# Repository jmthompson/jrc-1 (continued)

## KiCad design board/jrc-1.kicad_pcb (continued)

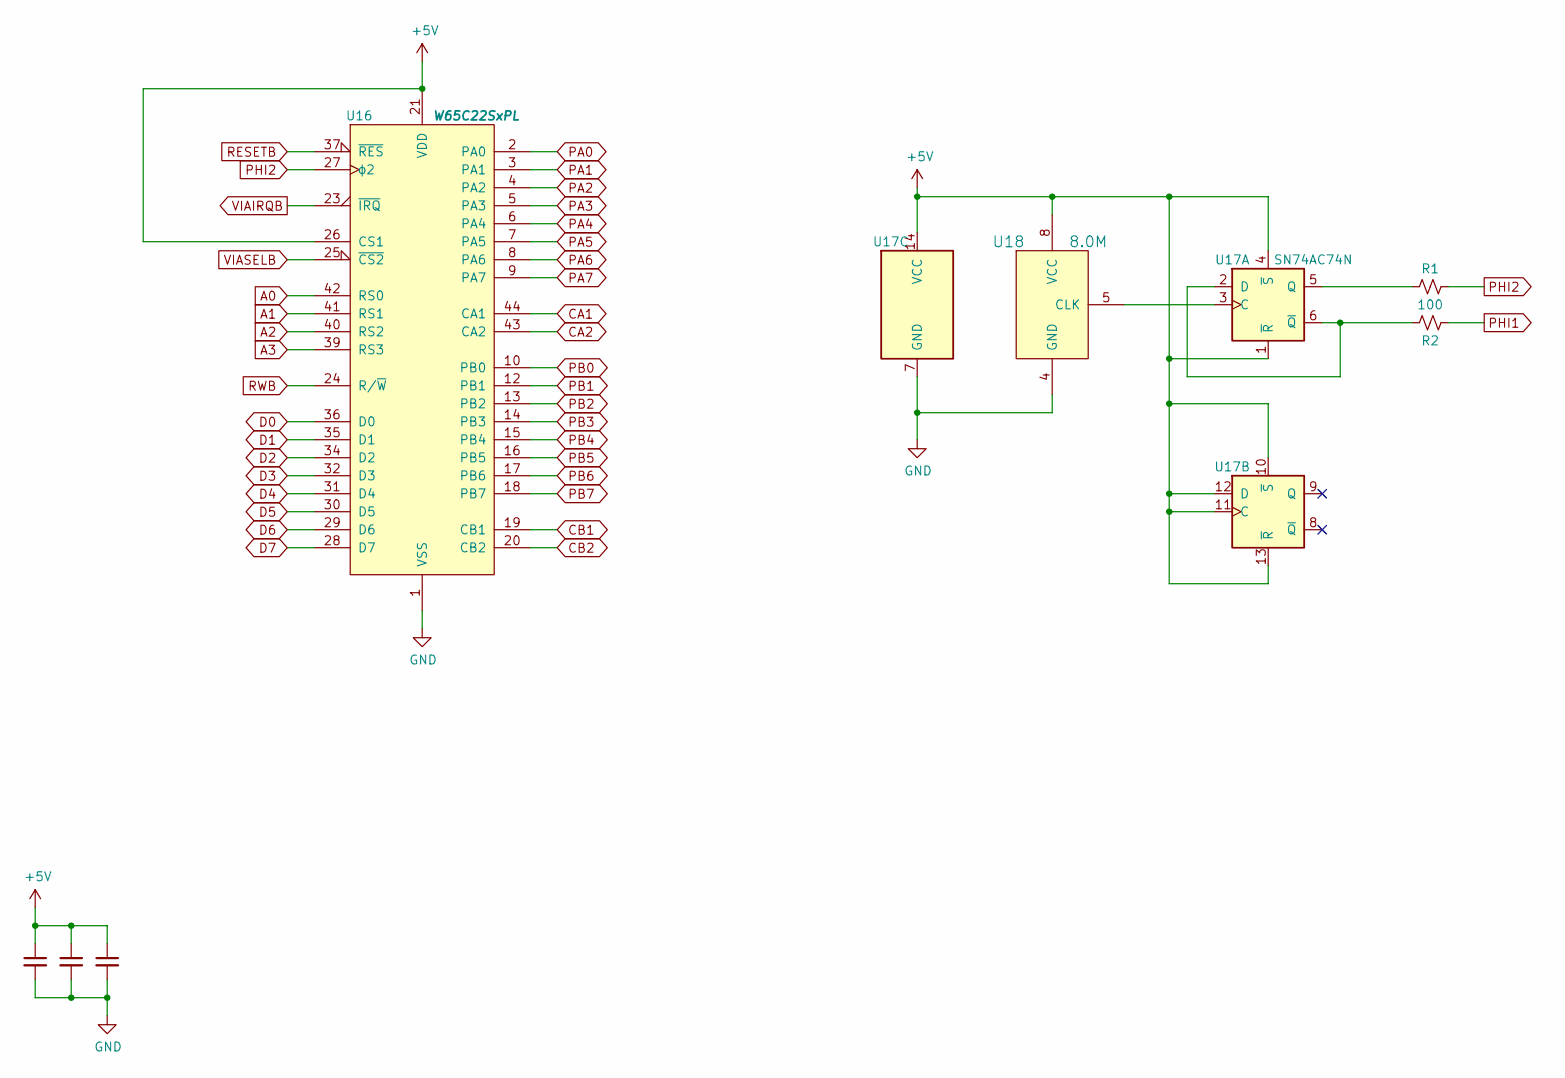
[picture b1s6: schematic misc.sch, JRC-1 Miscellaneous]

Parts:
C35, C36, C37: 0.1u; C_Rect_L4.6mm_W2.0mm_P2.50mm_MKS02_FKP02
R1, R2: 100; R_Axial_DIN0207_L6.3mm_D2.5mm_P10.16mm_Horizontal
U16: W65C22SxPL; PLCC-44_THT-Socket
U17: SN74AC74N; DIP-14_W7.62mm_Socket
U18: 8.0M; DIP-8_W7.62mm_Socket

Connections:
+5V: C35.1, C36.1, C37.1, U16.21 (VDD), U16.26 (CS1), U17.1 (~R), U17.4 (~S), U17.10 (~S), U17.11 (C), U17.12 (D), U17.13 (~R), U17.14 (VCC), U18.8 (VCC); also elsewhere on the board
A0: U16.42 (RS0); also elsewhere on the board
A1: U16.41 (RS1); also elsewhere on the board
A2: U16.40 (RS2); also elsewhere on the board
A3: U16.39 (RS3); also elsewhere on the board
CA1: U16.44 (CA1); also elsewhere on the board
CA2: U16.43 (CA2); also elsewhere on the board
CB1: U16.19 (CB1); also elsewhere on the board
CB2: U16.20 (CB2); also elsewhere on the board
D0: U16.36 (D0); also elsewhere on the board
D1: U16.35 (D1); also elsewhere on the board
D2: U16.34 (D2); also elsewhere on the board
D3: U16.32 (D3); also elsewhere on the board
D4: U16.31 (D4); also elsewhere on the board
D5: U16.30 (D5); also elsewhere on the board
D6: U16.29 (D6); also elsewhere on the board
D7: U16.28 (D7); also elsewhere on the board
GND: C35.2, C36.2, C37.2, U16.1 (VSS), U17.7 (GND), U18.4 (GND); also elsewhere on the board
unnamed: R1.2, U17.5 (Q)
unnamed: R2.2, U17.2 (D), U17.6 (~Q)
unnamed: U17.3 (C), U18.5 (CLK)
PA0: U16.2 (PA0); also elsewhere on the board
PA1: U16.3 (PA1); also elsewhere on the board
PA2: U16.4 (PA2); also elsewhere on the board
PA3: U16.5 (PA3); also elsewhere on the board
PA4: U16.6 (PA4); also elsewhere on the board
PA5: U16.7 (PA5); also elsewhere on the board
PA6: U16.8 (PA6); also elsewhere on the board
PA7: U16.9 (PA7); also elsewhere on the board
PB0: U16.10 (PB0); also elsewhere on the board
PB1: U16.12 (PB1); also elsewhere on the board
PB2: U16.13 (PB2); also elsewhere on the board
PB3: U16.14 (PB3); also elsewhere on the board
PB4: U16.15 (PB4); also elsewhere on the board
PB5: U16.16 (PB5); also elsewhere on the board
PB6: U16.17 (PB6); also elsewhere on the board
PB7: U16.18 (PB7); also elsewhere on the board
PHI1: R2.1; also elsewhere on the board
PHI2: R1.1, U16.27 (ϕ2); also elsewhere on the board
RESETB: U16.37 (~RES); also elsewhere on the board
RWB: U16.24 (R/~W); also elsewhere on the board
VIAIRQB: U16.23 (~IRQ); also elsewhere on the board
VIASELB: U16.25 (~CS2); also elsewhere on the board

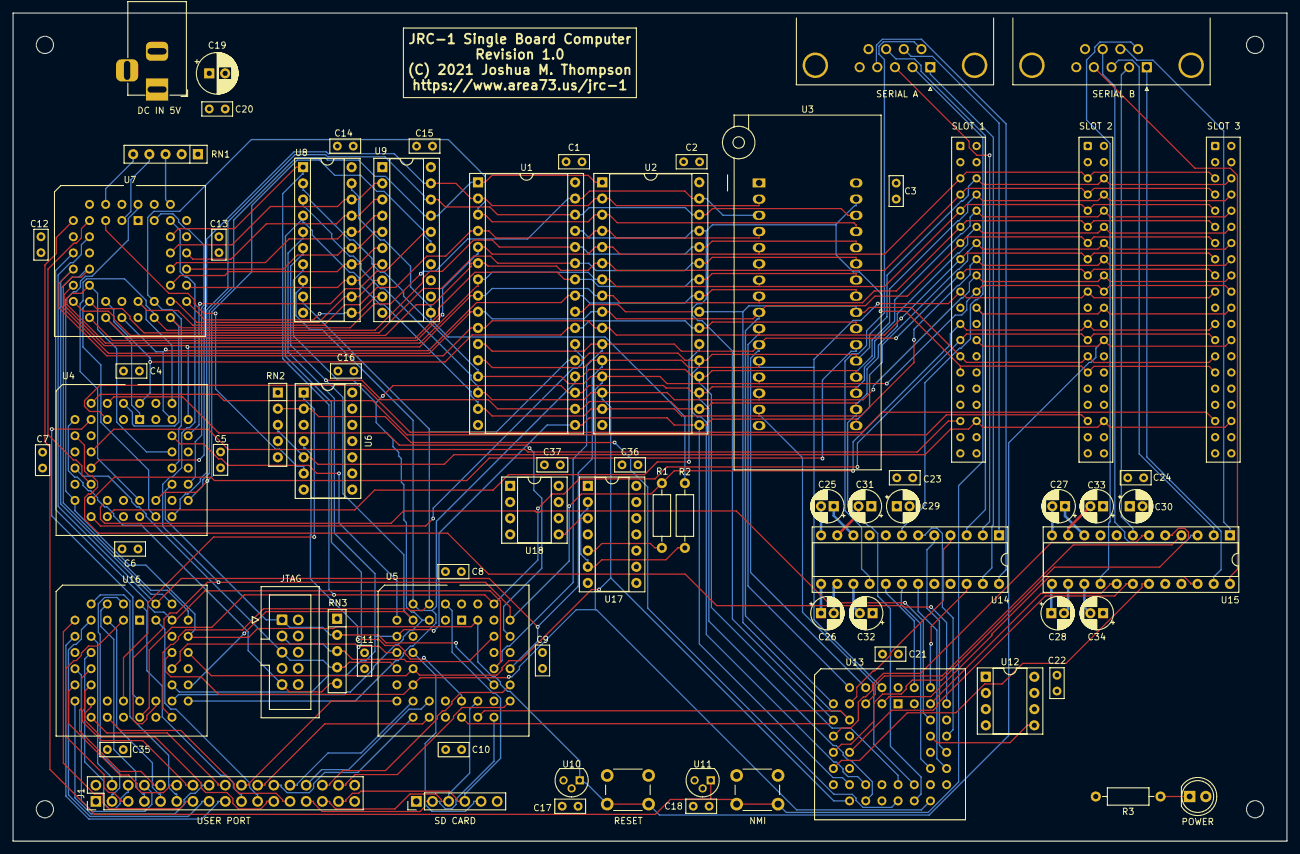
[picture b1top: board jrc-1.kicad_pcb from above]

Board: 4 copper layers, 200.0 x 130.0 mm, 77 parts (0 on the bottom side), 147 nets.

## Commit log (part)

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2021-09-03 Design files for JIGL custom CPLD, and beginning board schematic
2021-12-11 RC1 of schematic and initial board layout
2021-12-11 Use custom footprint for slots to get more favorable pin numbering for layout purposes.
2021-12-24 Fix footprint for RESET and NMI button handlers Fix symbol for '573 latch
2021-12-28 Remove the ROM flasher as it's not suitable for this design
2021-12-28 Split bios.s into smaller, more manageable files.
    Adjust the memory map configuration so that the area in bank $10 below
    the $F800 ROM is now used for the OS code, leaving the rest free for
    built-in applications and whatnot.
2021-12-28 Move syscall dispatcher up to the OSROM area to give more room for the dispatch cable to grow.
2021-12-29 Flesh out more of the device manager Register the serial ports as devices Merge vt100_console.s into console.s Console now attaches to serial devices via device manager Moved getc_serialX and putc_se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
2022-01-09 Remove console_readln and associated syscall, and move the code into the monitor as it's the only actual user of this function.
    Fully populate syscall table with 256 entries instead of checking
    syscall_max. This is a prelude to moving the dispatch table into RAM so
    that it can be patched at runtime.
2022-01-09 Change monitor's address parsing to work more like the GS monitor. Addresses are now BB/XXYY, and addresses without a bank byte will use the current bank byte value.
    Remove '>' from monitor prompt
2022-01-09 Move a bunch of useful utliity functions out of monitor.s and into util.s, to make them easier to share with other interactive pieces of the system ROM.
2022-01-09 Allow commands to be upper or lower case.
2022-01-09 Rip out all the character device definitions, and streamline the console calls.
2022-01-09 Explicitly send CRLF to terminate lines for full VT100 compatibility
2022-01-10 Beginning of reorganization of syscalls:
    - Move dispatch code to interrupts.s; syscalls.s is now just the table
    - Add some new console calls
    - Remove device manager calls
    - Add SPI calls
2022-01-10 Separate interrupt and normal OS contexts so that interrupts run with the data bank in bank 0, but the rest of the OS runs with the data bank set to the SYSRAM bank (normally $01). This configuration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
2022-01-11 Fix code to use far addresing for 65SPI registers now that DB is no onger in bank 0 outside of interrupts.
2022-01-11 Fix inverted slave select logic and incorrect SS4-SS7 constants
2022-01-12 Switch to external clock input, which is bodge wired to VIA PB7. This allows us to init SD cards at a slower rate than PHI2.
2022-01-12 Direct page cleanups
2022-01-12 Change data bank to SYSDATA segment at startup
2022-01-12 Make JR/OS initialization partially work again. Fixed up old 8-bit code in a number of places as well.
    Fix SD card driver init and status calls. They now work...usually.
2022-01-12 Add ability to switch between slow (400 kHZ) and fast (phi2) SPI clocks. The default is back to fast mode, with the SD card driver temporarily setting slow mode during card initialization.
2022-01-13 Updates to sdc_rdblock and sdc_wrblock; both seem to work reliably now.
2022-01-13 Forgotten bits from previous commits.
2022-01-13 WIP JR/OS device enumeration
2022-01-15 Change startup banner to show JR/OS version and remove separate JR/OS banner.
2022-01-16 Add print_decimal32 routine
2022-01-16 Fix buggy zero suppression in print_decimal32
2022-01-16 Fix card type checking
2022-01-16 Print device size during device scan
2022-01-17 Remove device driver mount call Add retry logic to sdc_init Fix param byte counts for JR/OS syscalls.
2022-01-28 Reorganize src folder into subfolders
2022-01-28 Add some documentation
2022-02-23 Move all buffers from into the SYSDATA segment, freeing up about 1.5k more bank 0 space.
2022-02-23 Move syscall table to its own segment at a fixed location.
2022-02-24 Refactor syscall dispatching to put a pointer to the caller's params frame into the global zp location "params", instead of just supporting 0 or 1 parameter.
2022-02-24 Initial work on defaulting syscalls to run in full 16-bit mode:
    - Make most of syscall dispatch 16-bit now, by expanding a few 3-byte
    fields to 4-bytes
    - Make the serial send/receive methods explicitly set 8-bit mode and
    restore previous mode on exit.
2022-02-25 Add new syscall handler macros; these will be used to transition all existing sycall handlers to the new 16-bit model.
2022-03-02 Make syscalls reentertant by saving and restoring the params pointer.
2022-03-13 Add a device manager subsystem to manage character and block devices. At the moment only the SPI and SDCARD drivers have been converted to this new framework; serial and console drivers will follow.
2022-03-13 Remove OPEN and CLOSE for block devices and add a MOUNT call.
    Update the sdcard driver so that STARTUP always succeeds, making sure
    the driver is installed even if no card is present at boot time. A
    subsequent MOUNT call can be used to initialize the card.
2022-03-14 Add bootup device scan and volume scans.
2022-05-01 Move disassembler constants into monitor source tree
2022-05-01 Rename syscalls.inc to syscall_macros.inc to better describe its contents
2022-05-01 Include file reorg.
2022-05-08 Move print_decimal8 function into the startup code, as that is the only thing using it. The rest of util.s now belongs to the monitor.
2022-05-08 Add LF to the NMI/BRK banners so they aren't overwritten by the register dump
2022-05-08 add # command for dumping captured register contents
2022-05-10 Fix illegal addressing mode error in PushWord/PushLong macros Add definitions for status register bits
2022-05-11 Split util.s uip by function, and move them to a new lib folder.
2022-05-18 Update print_decimal32 to use stack local variables instead of memory in SYDATA, and also make it callable with any register widths
2022-05-18 Add _GetChar macro
2022-05-19 Replace original print_decimal32 with format_decimal, which renders to an output buffer instead of directly to console, and supports more formatting options.
2022-05-19 Update run_code to call code in 16-bit mode, and to set registers before the call and capture their new values on return.
2022-05-21 Initial pass at making the monitor default to 16-bit registers.
2022-05-21 Remove use of inc32 on ibuffp since it's never going to cross a bank boundary.
2022-05-23 Add abilty to modify the values of registers before calling code.
2022-09-11 Adjust T1 constant for 400 kHz SPI clock generation to account for the board now running at 8 MHz
2022-09-19 Rename SYSDATA segment to BSS
2022-09-25 Add multiply_8x8 function to library
2022-10-11 Fix crash after a syntax error due to missing longm
2022-10-12 Remove uneeded shortmx/longmx instructions during startup since the monitor is 16-bit clean now.
2022-10-12 Refactor syscall dispatch to set local direct page again instead of setting params dp location
2022-10-13 Initial round of trying to find a less painful way to set up syscalls and eal with stack-based parameters.
2022-10-17 Allow PARAM macro to be used in standalone functions by allowing the starting DP offset to be changed
2022-10-19 Add memory management subsystem and associated syscalls.
    Add monitor 'h' command for dumping the internal memory manager handle lists.
2022-10-19 Fix set_memory to not store an extra -bash0 on every write
2022-10-22 Rename disasm_constants.s to opcodes.inc
    Update syscall names table
2022-10-22 Remove things from the directpage that don't realy need to be there and move them into the BSS segment.
2022-10-22 Make string argument to _PrintString optional.
2022-10-22 Restore ^ pointer on syntax errors Allow specifying max digit limit to parse_hex again.
2022-12-31 Add miniassembler
2022-12-31 Fix typo in comment
2022-12-31 Separate the include files so that files not usable in user space are in the kernel/ subdirectory
2022-12-31 - Add syscalls for returning uptime and system version
    - Add syscall for rebooting the system
    - Add syscall for entering the monitor
    - Remove hardware version from boot screen
    - Change JR/OS version to 16-bits to allow for x.y.z format
2023-01-02 Remove all in-kernel calls to the console driver and replace them with new _kputc and _kprint macros. internally both call putc_seriala directly. These new macros are only used in the actual kernel c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
2023-01-15 Add missing include file
2023-01-16 Rename JR/OS to jrcOS in all files.
2023-01-17 Fix bug in wait_ms causing it to not work when DB is not -bash0
2023-01-29 Zero out the BSS segment at startup
2023-03-08 Remove existing DOS skeleton code and device manager syscalls in prep for switch to new device model.
2023-03-08 Remove memory manager and associated syscalls
2023-03-08 Add kernel heap management code
2023-03-08 Add skeletal framework for process support and scheduler
2023-03-08 Remove longaddr macro and replace with standard .dword directive Add macros for conditional jumps
2023-03-09 Add generic functions for managing arrays of refcounted objects. Add heap_init call to startup
2023-03-09 Reduce OS stack to 256 bytes and fix USERRAM to not overlap the heap
2023-03-10 Refactor COP dispatcher to use the OS direct page instead of a stack local one.
2023-03-28 Move non-syscalls over to the new function macros
2023-04-04 Implement new paradigm for getting and returning parameters from syscalls.
2023-04-06 Mega-patch:
    - New driver architecture
    - All old console/serial port syscalls removed
    - Add initial support for filesystem and FS syscalls
    - Update monitor to open /dev/console as stdin,stdout,stderr
    - stdlib functions that access console now use stdin and stdout
2023-04-07 Change cop dispatcher to automatically return ERR_NOT_SUPPORTED if the syscall being made has a null handler in the syscall table.
2023-04-12 Change error definitions to use standard Unix C names, and make them be negative 16-bit numbers
2023-04-30 Move the COP stack frame definition into a global struct definition.
2024-12-26 Fix memory dumper bug and add disassembler
2024-12-31 More monitor additions: added run code, and fixed bugs in set memory and set register commands.
2024-12-31 Add define for SIMPLE_CALL to silence additional false errors in VS Code.
2025-01-13 Restore missing functionality to the system monitor.
2025-01-14 Move Intellisense #defines into a kernel-wide header.
2025-01-15 Remove extern from SIMPLE_CALL on Intellisense
2025-01-18 Move mem_addr_t and friends into main kernel types.h
2025-01-18 Add kprintf variants to console.h and remove printf.h
2025-01-18 printf -> kprintf Add (H) command to dump the heap structure. Fix M/X tracking in disassembler. Cleanup some old commented out assembly code.
2025-01-18 Additional WIP on the whole driver/disk/fs infrastructure.
2025-10-01 Version bump
2025-10-05 Move the jrcos/stdlib to the main level, and make it generate a library that is usable by both jrcos and ROM apps.
2025-10-05 Remove hard-coded stdlib.bin reference
2025-10-06 Working bare bones scheduler implementation. The system startup code no longer invokes the monitor, but instead sets it up as the single running task and calling the scheduler to reschedule into it.
2025-10-06 Create an idle_task that runs at startup and when nothing else is running.
2025-10-17 Add SYS_EXIT call.
2025-10-17 Scheduler updates
2025-11-10 Major overhaul:
    - Convert code that accesses objects in the kernel data bank to use
    16-bit addressing instead of 24-bit.
    - Changed size_t from 32-bit to 16-bit.
    - Scheduler now keeps a double linked list of active tasks. This
    prevents a potential full scan of the task list on reschedule.
2026-03-30 fix: Fix crashes in Xmodem code
2026-04-03 fix: Update getchar() to return correct status when no data was read
2026-04-03 fix: Change monitor to oppen stdin in non-blocking mode
